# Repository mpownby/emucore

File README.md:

emucore
=======

Permissive high-quality emulation-related code

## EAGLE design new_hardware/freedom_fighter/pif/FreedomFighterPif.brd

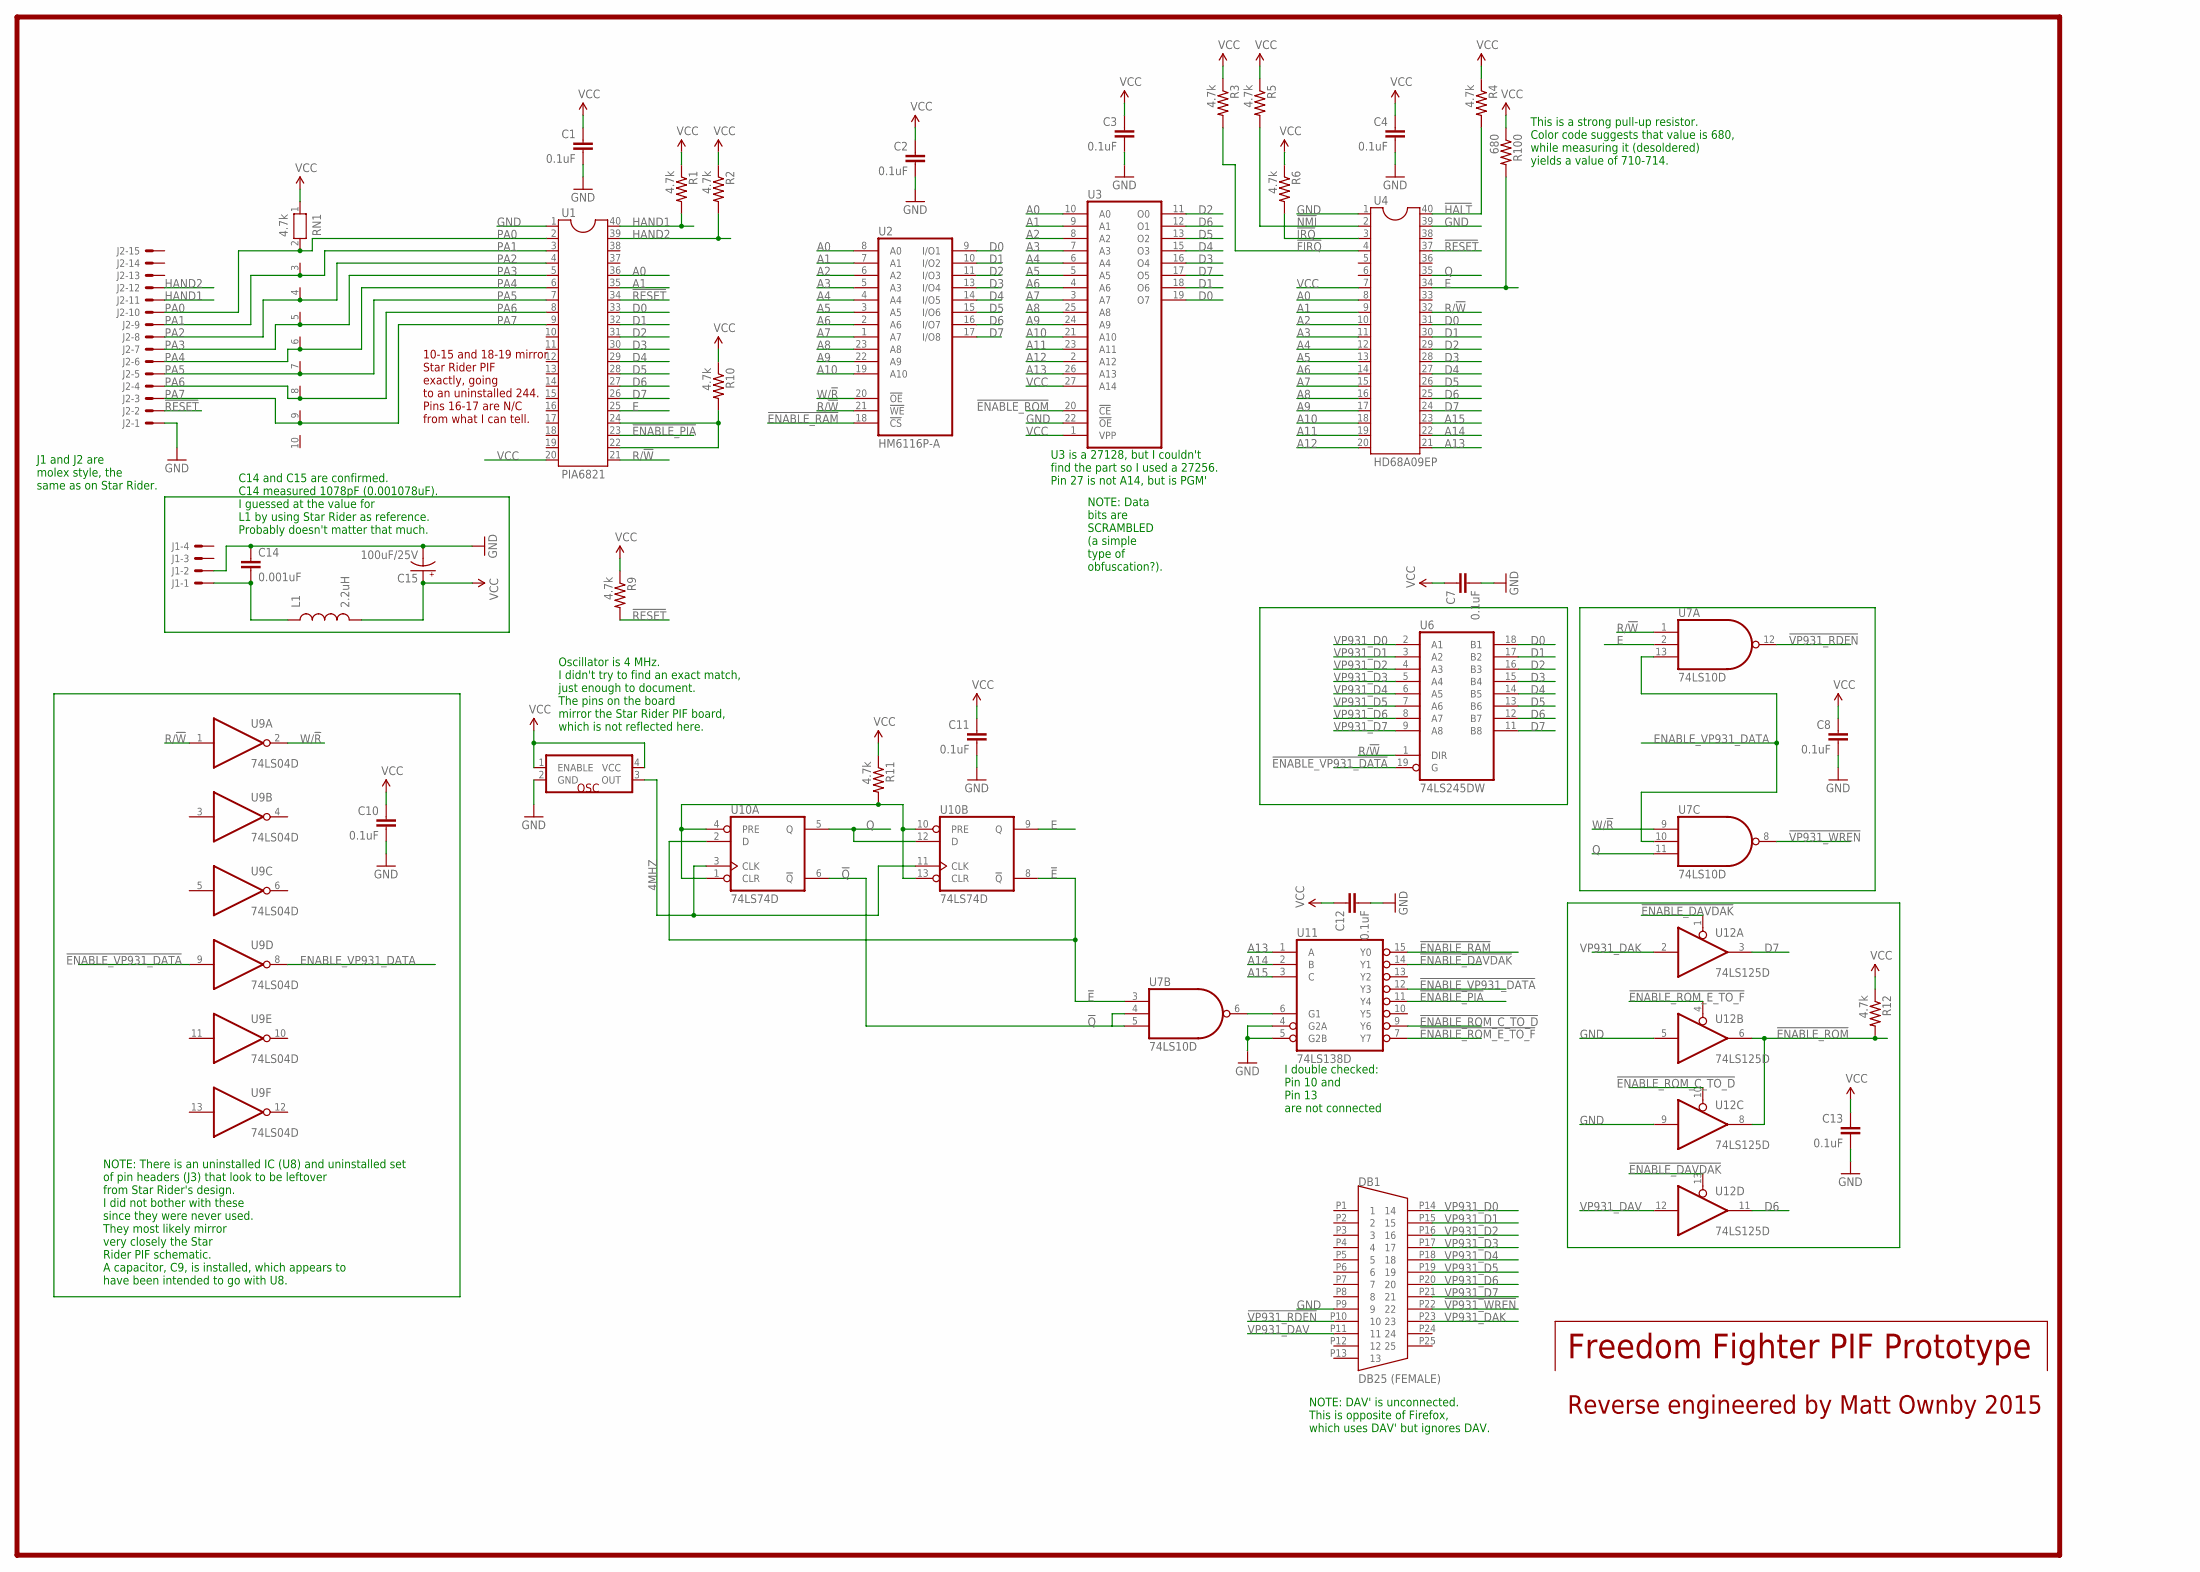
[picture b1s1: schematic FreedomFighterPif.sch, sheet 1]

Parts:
C1, C2, C3, C4, C7, C8, C10, C11, C12, C13: 0.1uF; 1206
C14: 0.001uF; 1206
C15: 100uF/25V; CPOL-RADIAL-10UF-25V
DB1: DB25 (FEMALE); A32077-ND
J1: KK-156-4
J2: KK-156-15
L1: 2.2uH; INDUCTOR-1206
R1, R2, R3, R4, R5, R6, R9, R10, R11, R12: 4.7k; 1206
R100: 680; 1206
RN1: 4.7k; RN-10
U1: PIA6821; DIL40
U2: HM6116P-A; SO24-2
U3: 27256; DIL28
U4: HD68A09EP; DIL40
U6: 74LS245DW; SO20W
U7: 74LS10D; SO14
U9: 74LS04D; SO14
U10: 74LS74D; SO14
U11: 74LS138D; SO16
U12: 74LS125D; SO14
U$1: OSCILLATOR-SMT4; SMT4-7MMX5MM

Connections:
4MHZ: U10.3 (CLK), U10.11 (CLK), U$1.3 (OUT)
!E: U7.3 (I0), U10.2 (D), U10.8 (!Q)
!ENABLE_DAVDAK: U11.14 (Y1), U12.1 (OE), U12.13 (OE); also elsewhere on the board
!ENABLE_PIA: U1.23, U11.11 (Y4); also elsewhere on the board
!ENABLE_RAM: U2.18 (!CS), U11.15 (Y0); also elsewhere on the board
!ENABLE_ROM: R12.2, U3.20 (!CE), U12.6 (O), U12.8 (O)
!ENABLE_ROM_C_TO_D: U11.9 (Y6), U12.10 (OE); also elsewhere on the board
!ENABLE_ROM_E_TO_F: U11.7 (Y7), U12.4 (OE); also elsewhere on the board
!ENABLE_VP931_DATA: U6.19 (G), U9.9 (I), U11.12 (Y3); also elsewhere on the board
!FIRQ: R3.2, U4.4; also elsewhere on the board
!HALT: R4.2, U4.40; also elsewhere on the board
!IRQ: R6.2, U4.3; also elsewhere on the board
!NMI: R5.2, U4.2; also elsewhere on the board
!Q: U7.4 (I1), U7.5 (I2), U10.6 (!Q)
!RESET: J2.2, R9.2, U1.34, U4.37; also elsewhere on the board
!VP931_RDEN: DB1.P10 (10), U7.12 (O)
!VP931_WREN: DB1.P22 (22), U7.8 (O)
A0: U1.36, U2.8 (A0), U3.10 (A0), U4.8; also elsewhere on the board
A1: U1.35, U2.7 (A1), U3.9 (A1), U4.9; also elsewhere on the board
A2: U2.6 (A2), U3.8 (A2), U4.10; also elsewhere on the board
A3: U2.5 (A3), U3.7 (A3), U4.11; also elsewhere on the board
A4: U2.4 (A4), U3.6 (A4), U4.12; also elsewhere on the board
A5: U2.3 (A5), U3.5 (A5), U4.13; also elsewhere on the board
A6: U2.2 (A6), U3.4 (A6), U4.14; also elsewhere on the board
A7: U2.1 (A7), U3.3 (A7), U4.15; also elsewhere on the board
A8: U2.23 (A8), U3.25 (A8), U4.16; also elsewhere on the board
A9: U2.22 (A9), U3.24 (A9), U4.17; also elsewhere on the board
A10: U2.19 (A10), U3.21 (A10), U4.18; also elsewhere on the board
A11: U3.23 (A11), U4.19; also elsewhere on the board
A12: U3.2 (A12), U4.20; also elsewhere on the board
A13: U3.26 (A13), U4.21, U11.1 (A); also elsewhere on the board
A14: U4.22, U11.2 (B); also elsewhere on the board
A15: U4.23, U11.3 (C); also elsewhere on the board
CS0/CS1: R10.2, U1.22, U1.24
D0: U1.33, U2.9 (I/O1), U3.19 (O7), U4.31, U6.18 (B1); also elsewhere on the board
D1: U1.32, U2.10 (I/O2), U3.18 (O6), U4.30, U6.17 (B2); also elsewhere on the board
D2: U1.31, U2.11 (I/O3), U3.11 (O0), U4.29, U6.16 (B3); also elsewhere on the board
D3: U1.30, U2.13 (I/O4), U3.16 (O4), U4.28, U6.15 (B4); also elsewhere on the board
D4: U1.29, U2.14 (I/O5), U3.15 (O3), U4.27, U6.14 (B5); also elsewhere on the board
D5: U1.28, U2.15 (I/O6), U3.13 (O2), U4.26, U6.13 (B6); also elsewhere on the board
D6: U1.27, U2.16 (I/O7), U3.12 (O1), U4.25, U6.12 (B7), U12.11 (O); also elsewhere on the board
D7: U1.26, U2.17 (I/O8), U3.17 (O5), U4.24, U6.11 (B8), U12.3 (O); also elsewhere on the board
E: R100.2, U1.25, U4.34, U7.2 (I1), U10.9 (Q); also elsewhere on the board
ENABLE_VP931_DATA: U7.10 (I1), U7.13 (I2), U9.8 (O); also elsewhere on the board
GND: C1.2, C2.2, C3.2, C4.2, C7.2, C8.2, C10.2, C11.2, C12.2, C13.2, C14.1, C15.2 (-), DB1.P9 (9), J1.2, J2.1, U1.1, U2.12 (GND), U3.14 (GND), U3.22 (!OE), U4.1, U4.39, U6.10 (GND), U7.7 (GND), U9.7 (GND), U10.7 (GND), U11.4 (G2A), U11.5 (G2B), U11.8 (GND), U12.5 (I), U12.7 (GND), U12.9 (I), U$1.2 (GND); also elsewhere on the board
HAND1: J2.11, R1.2, U1.40; also elsewhere on the board
HAND2: J2.12, R2.2, U1.39; also elsewhere on the board
unnamed: U7.6 (O), U11.6 (G1)
unnamed: R11.2, U10.1 (CLR), U10.4 (PRE), U10.10 (PRE), U10.13 (CLR)
unnamed: C14.2, J1.1, L1.P$1 (1)
PA0: J2.10, RN1.2, U1.2; also elsewhere on the board
PA1: J2.9, RN1.3, U1.3; also elsewhere on the board
PA2: J2.8, RN1.4, U1.4; also elsewhere on the board
PA3: J2.7, RN1.5, U1.5; also elsewhere on the board
PA4: J2.6, RN1.6, U1.6; also elsewhere on the board
PA5: J2.5, RN1.7, U1.7; also elsewhere on the board
PA6: J2.4, RN1.8, U1.8; also elsewhere on the board
PA7: J2.3, RN1.9, U1.9; also elsewhere on the board
Q: U4.35, U7.11 (I2), U10.5 (Q), U10.12 (D); also elsewhere on the board
R/!W: U1.21, U2.21 (!WE), U4.32, U6.1 (DIR), U7.1 (I0), U9.1 (I); also elsewhere on the board
VCC: C1.1, C2.1, C3.1, C4.1, C7.1, C8.1, C10.1, C11.1, C12.1, C13.1, C15.1 (+), L1.P$2 (2), R1.1, R2.1, R3.1, R4.1, R5.1, R6.1, R9.1, R10.1, R11.1, R12.1, R100.1, RN1.1, U1.20, U2.24 (VCC), U3.1 (VPP), U3.27 (A14), U3.28 (VCC), U4.7, U6.20 (VCC), U7.14 (VCC), U9.14 (VCC), U10.14 (VCC), U11.16 (VCC), U12.14 (VCC), U$1.1 (ENABLE), U$1.4 (VCC); also elsewhere on the board
VP931_D0: DB1.P14 (14), U6.2 (A1)
VP931_D1: DB1.P15 (15), U6.3 (A2)
VP931_D2: DB1.P16 (16), U6.4 (A3)
VP931_D3: DB1.P17 (17), U6.5 (A4)
VP931_D4: DB1.P18 (18), U6.6 (A5)
VP931_D5: DB1.P19 (19), U6.7 (A6)
VP931_D6: DB1.P20 (20), U6.8 (A7)
VP931_D7: DB1.P21 (21), U6.9 (A8)
VP931_DAK: DB1.P23 (23), U12.2 (I)
VP931_DAV: DB1.P11 (11), U12.12 (I)
W/!R: U2.20 (!OE), U7.9 (I0), U9.2 (O); also elsewhere on the board

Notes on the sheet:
U3 is a 27128, but I couldn't find the part so I used a 27256. Pin 27 is not A14, but is PGM'
NOTE: Data bits are SCRAMBLED (a simple type of obfuscation?).
I double checked: Pin 10 and Pin 13 are not connected
NOTE: There is an uninstalled IC (U8) and uninstalled set of pin headers (J3) that look to be leftover from Star Rider's design. I did not bother with these since they were never used. They most likely mirror very closely the Star Rider PIF schematic. A capacitor, C9, is installed, which appears to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
NOTE: DAV' is unconnected. This is opposite of Firefox, which uses DAV' but ignores DAV.
Oscillator is 4 MHz. I didn't try to find an exact match, just enough to document. The pins on the board mirror the Star Rider PIF board, which is not reflected here.
C14 and C15 are confirmed. C14 measured 1078pF (0.001078uF). I guessed at the value for L1 by using Star Rider as reference. Probably doesn't matter that much.
Freedom Fighter PIF Prototype
Reverse engineered by Matt Ownby 2015
10-15 and 18-19 mirror Star Rider PIF exactly, going to an uninstalled 244. Pins 16-17 are N/C from what I can tell.
This is a strong pull-up resistor. Color code suggests that value is 680, while measuring it (desoldered) yields a value of 710-714.
J1 and J2 are molex style, the same as on Star Rider.

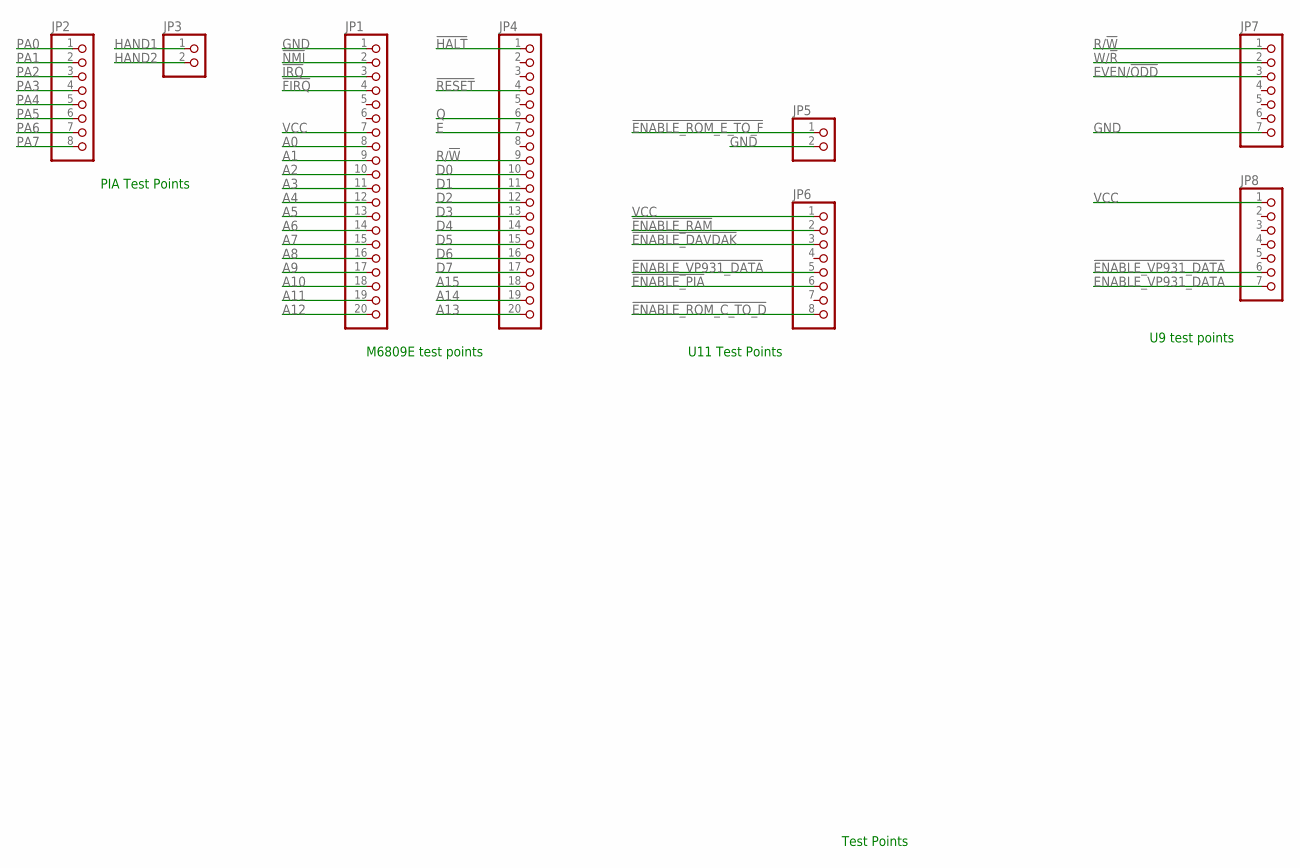
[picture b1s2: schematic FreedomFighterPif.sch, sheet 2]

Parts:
JP1, JP4: PINHD-1X20; 1X20
JP2, JP6: PINHD-1X8; 1X08
JP3, JP5: PINHD-1X2; 1X02
JP7, JP8: PINHD-1X7; 1X07

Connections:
!ENABLE_DAVDAK: JP6.3; also elsewhere on the board
!ENABLE_PIA: JP6.6; also elsewhere on the board
!ENABLE_RAM: JP6.2; also elsewhere on the board
!ENABLE_ROM_C_TO_D: JP6.8; also elsewhere on the board
!ENABLE_ROM_E_TO_F: JP5.1; also elsewhere on the board
!ENABLE_VP931_DATA: JP6.5, JP8.6; also elsewhere on the board
!FIRQ: JP1.4; also elsewhere on the board
!HALT: JP4.1; also elsewhere on the board
!IRQ: JP1.3; also elsewhere on the board
!NMI: JP1.2; also elsewhere on the board
!RESET: JP4.4; also elsewhere on the board
A0: JP1.8; also elsewhere on the board
A1: JP1.9; also elsewhere on the board
A2: JP1.10; also elsewhere on the board
A3: JP1.11; also elsewhere on the board
A4: JP1.12; also elsewhere on the board
A5: JP1.13; also elsewhere on the board
A6: JP1.14; also elsewhere on the board
A7: JP1.15; also elsewhere on the board
A8: JP1.16; also elsewhere on the board
A9: JP1.17; also elsewhere on the board
A10: JP1.18; also elsewhere on the board
A11: JP1.19; also elsewhere on the board
A12: JP1.20; also elsewhere on the board
A13: JP4.20; also elsewhere on the board
A14: JP4.19; also elsewhere on the board
A15: JP4.18; also elsewhere on the board
D0: JP4.10; also elsewhere on the board
D1: JP4.11; also elsewhere on the board
D2: JP4.12; also elsewhere on the board
D3: JP4.13; also elsewhere on the board
D4: JP4.14; also elsewhere on the board
D5: JP4.15; also elsewhere on the board
D6: JP4.16; also elsewhere on the board
D7: JP4.17; also elsewhere on the board
E: JP4.7; also elsewhere on the board
ENABLE_VP931_DATA: JP8.7; also elsewhere on the board
EVEN/!ODD: JP7.3
GND: JP1.1, JP5.2, JP7.7; also elsewhere on the board
HAND1: JP3.1; also elsewhere on the board
HAND2: JP3.2; also elsewhere on the board
PA0: JP2.1; also elsewhere on the board
PA1: JP2.2; also elsewhere on the board
PA2: JP2.3; also elsewhere on the board
PA3: JP2.4; also elsewhere on the board
PA4: JP2.5; also elsewhere on the board
PA5: JP2.6; also elsewhere on the board
PA6: JP2.7; also elsewhere on the board
PA7: JP2.8; also elsewhere on the board
Q: JP4.6; also elsewhere on the board
R/!W: JP4.9, JP7.1; also elsewhere on the board
VCC: JP1.7, JP6.1, JP8.1; also elsewhere on the board
W/!R: JP7.2; also elsewhere on the board

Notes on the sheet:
PIA Test Points
M6809E test points
U11 Test Points
U9 test points
Test Points

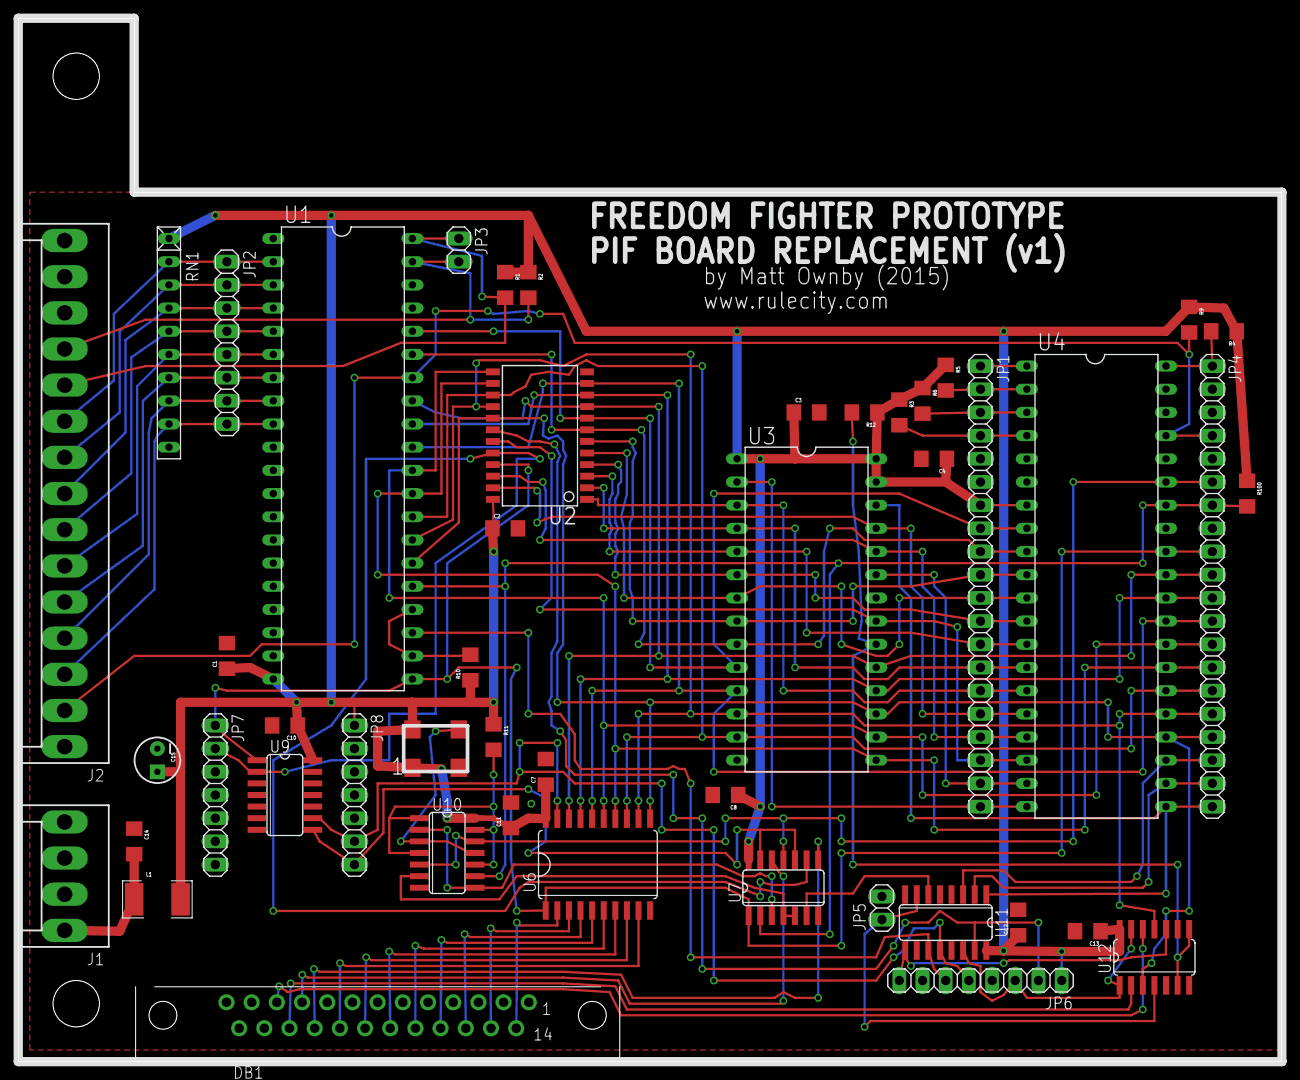
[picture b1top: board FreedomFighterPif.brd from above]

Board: 2 copper layers, 138.4 x 114.3 mm, 47 parts (0 on the bottom side), 72 nets.

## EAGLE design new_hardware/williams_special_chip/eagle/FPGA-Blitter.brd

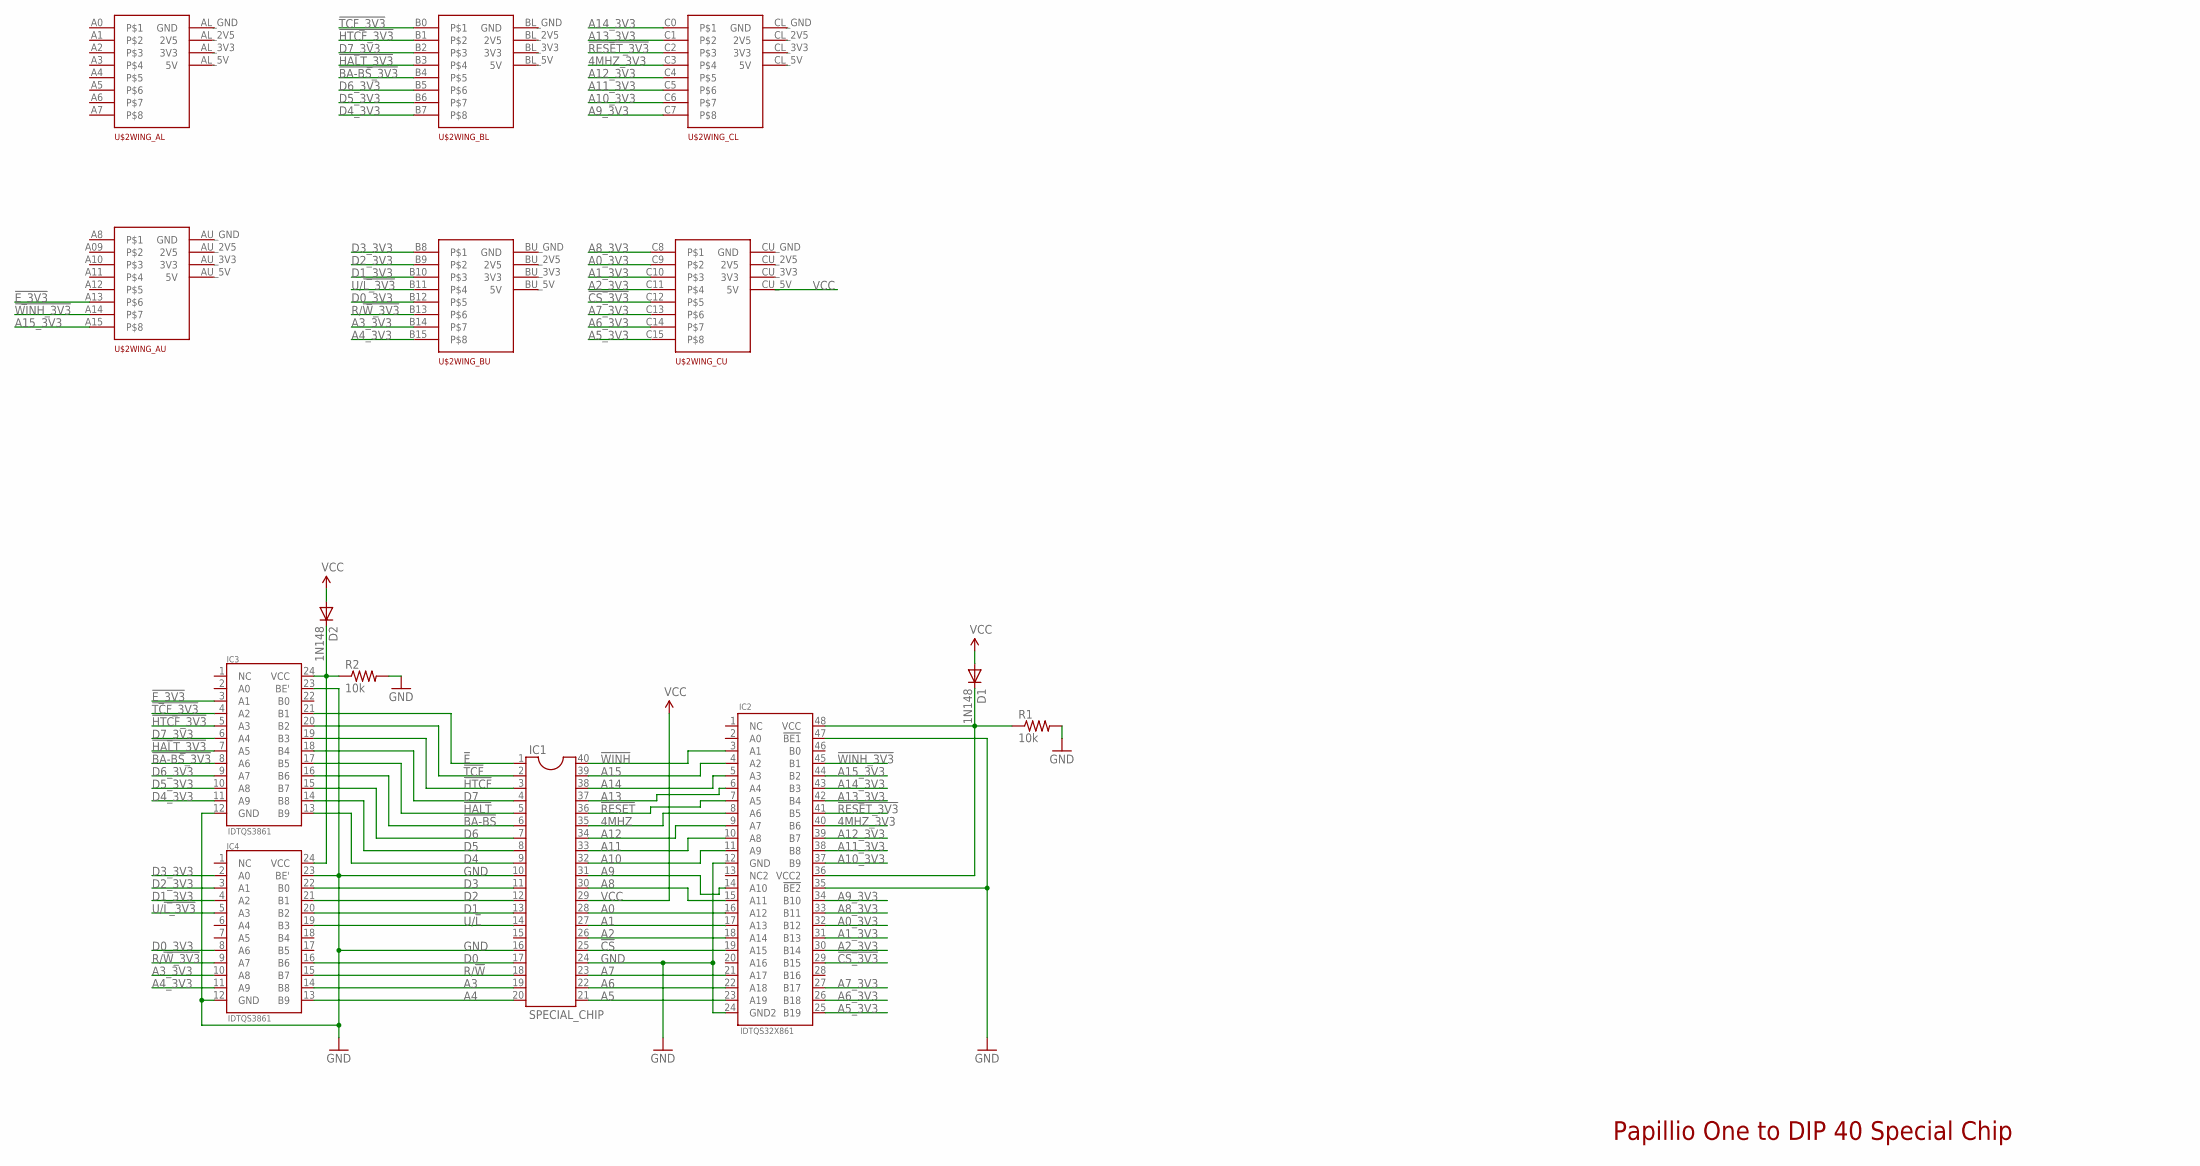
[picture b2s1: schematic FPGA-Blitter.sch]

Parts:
D1, D2: 1N148; DIODE-1N4148
IC1: SPECIAL_CHIP; DIL40
IC2: IDTQS32X861; QVSOP-DJG48-IDT
IC3, IC4: IDTQS3861; TSSOP24
R1, R2: 10k; 1206
U$2: PAPILIO48

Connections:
4MHZ: IC1.35, IC2.8 (A6)
4MHZ_3V3: IC2.40 (B6), U$2.C3
!BA-BS: IC1.6, IC3.16 (B6)
!BA-BS_3V3: IC3.8 (A6), U$2.B4
!CS: IC1.25, IC2.19 (A15)
!CS_3V3: IC2.29 (B15), U$2.C12
!E: IC1.1, IC3.21 (B1)
!E_3V3: IC3.3 (A1), U$2.A13
!HALT: IC1.5, IC3.17 (B5)
!HALT_3V3: IC3.7 (A5), U$2.B3
!HTCF: IC1.3, IC3.19 (B3)
!HTCF_3V3: IC3.5 (A3), U$2.B1
!RESET: IC1.36, IC2.7 (A5)
!RESET_3V3: IC2.41 (B5), U$2.C2
!TCF: IC1.2, IC3.20 (B2)
!TCF_3V3: IC3.4 (A2), U$2.B0
!WINH: IC1.40, IC2.3 (A1)
!WINH_3V3: IC2.45 (B1), U$2.A14
A0: IC1.28, IC2.16 (A12)
A0_3V3: IC2.32 (B12), U$2.C9
A1: IC1.27, IC2.17 (A13)
A1_3V3: IC2.31 (B13), U$2.C10
A2: IC1.26, IC2.18 (A14)
A2_3V3: IC2.30 (B14), U$2.C11
A3: IC1.19, IC4.14 (B8)
A3_3V3: IC4.10 (A8), U$2.B14
A4: IC1.20, IC4.13 (B9)
A4_3V3: IC4.11 (A9), U$2.B15
A5: IC1.21, IC2.23 (A19)
A5_3V3: IC2.25 (B19), U$2.C15
A6: IC1.22, IC2.22 (A18)
A6_3V3: IC2.26 (B18), U$2.C14
A7: IC1.23, IC2.21 (A17)
A7_3V3: IC2.27 (B17), U$2.C13
A8: IC1.30, IC2.15 (A11)
A8_3V3: IC2.33 (B11), U$2.C8
A9: IC1.31, IC2.14 (A10)
A9_3V3: IC2.34 (B10), U$2.C7
A10: IC1.32, IC2.11 (A9)
A10_3V3: IC2.37 (B9), U$2.C6
A11: IC1.33, IC2.10 (A8)
A11_3V3: IC2.38 (B8), U$2.C5
A12: IC1.34, IC2.9 (A7)
A12_3V3: IC2.39 (B7), U$2.C4
A13: IC1.37, IC2.6 (A4)
A13_3V3: IC2.42 (B4), U$2.C1
A14: IC1.38, IC2.5 (A3)
A14_3V3: IC2.43 (B3), U$2.C0
A15: IC1.39, IC2.4 (A2)
A15_3V3: IC2.44 (B2), U$2.A15
D0: IC1.17, IC4.16 (B6)
D0_3V3: IC4.8 (A6), U$2.B12
D1: IC1.13, IC4.20 (B2)
D1_3V3: IC4.4 (A2), U$2.B10
D2: IC1.12, IC4.21 (B1)
D2_3V3: IC4.3 (A1), U$2.B9
D3: IC1.11, IC4.22 (B0)
D3_3V3: IC4.2 (A0), U$2.B8
D4: IC1.9, IC3.13 (B9)
D4_3V3: IC3.11 (A9), U$2.B7
D5: IC1.8, IC3.14 (B8)
D5_3V3: IC3.10 (A8), U$2.B6
D6: IC1.7, IC3.15 (B7)
D6_3V3: IC3.9 (A7), U$2.B5
D7: IC1.4, IC3.18 (B4)
D7_3V3: IC3.6 (A4), U$2.B2
GND: IC1.10, IC1.16, IC1.24, IC2.12 (GND), IC2.24 (GND2), IC2.35 (!BE2), IC2.47 (!BE1), IC3.12 (GND), IC3.23 (BE'), IC4.12 (GND), IC4.23 (BE'), R1.2, R2.2
unnamed: D2.C, IC3.24 (VCC), IC4.24 (VCC), R2.1
unnamed: D1.C, IC2.36 (VCC2), IC2.48 (VCC), R1.1
R/!W: IC1.18, IC4.15 (B7)
R/!W_3V3: IC4.9 (A7), U$2.B13
U/!L: IC1.14, IC4.19 (B3)
U/!L_3V3: IC4.5 (A3), U$2.B11
VCC: D1.A, D2.A, IC1.29, U$2.CU_5V (5V)

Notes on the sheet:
Papillio One to DIP 40 Special Chip

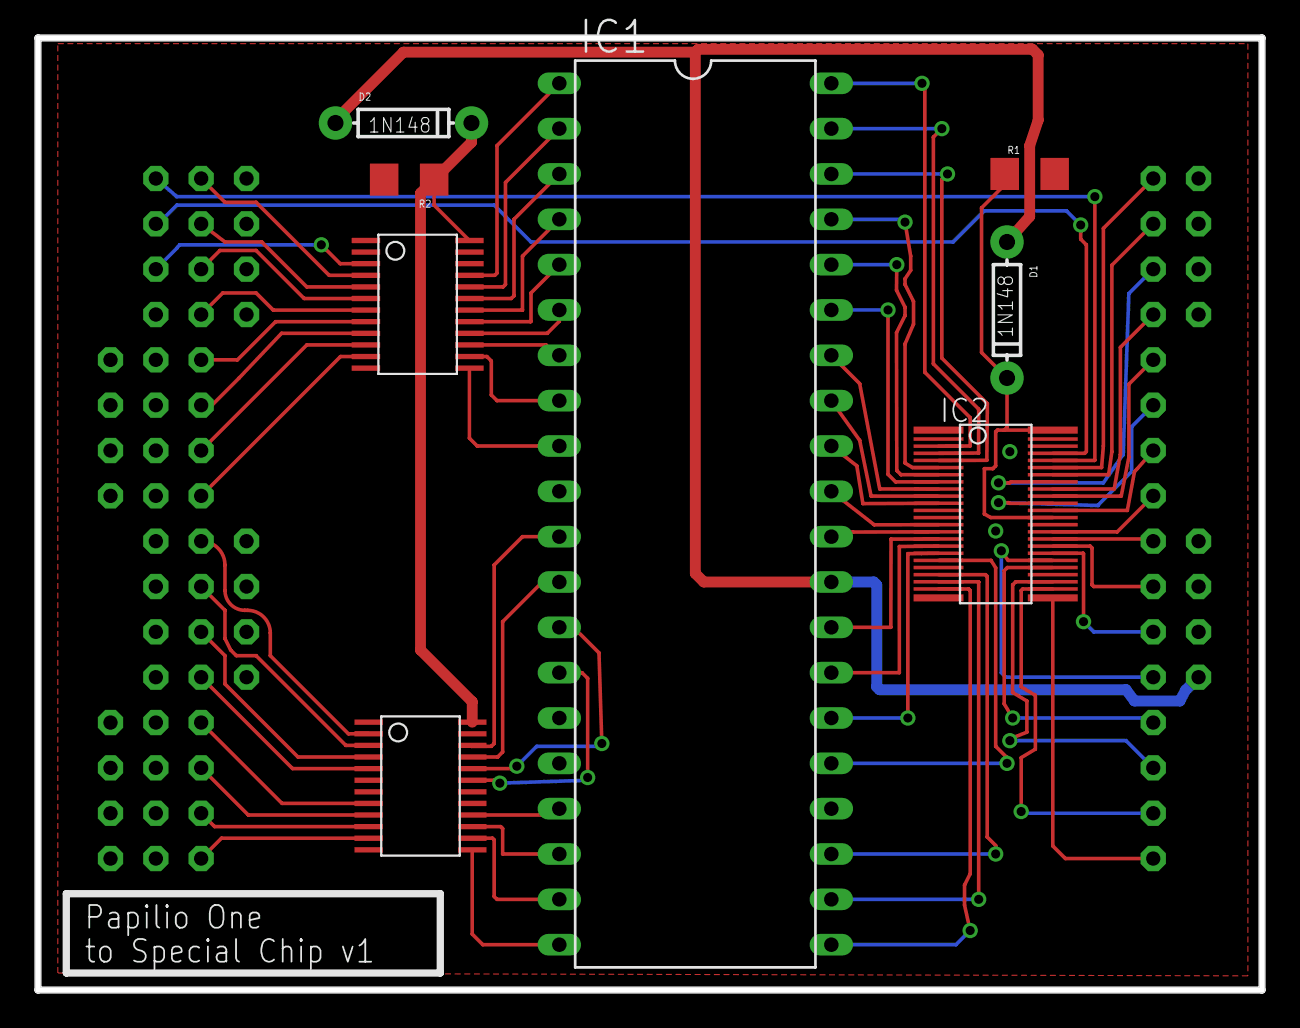
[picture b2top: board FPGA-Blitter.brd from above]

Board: 2 copper layers, 68.6 x 53.3 mm, 9 parts (1 on the bottom side), 74 nets.

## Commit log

2014-01-29 added IDA v3.85b ".idb" files of partial disassemblies that I've done over the years
2014-01-29 added proper segments for space ace .IDB file, added disassembly text file
2014-01-29 added star rider main cpu disassembly
2014-01-31 added a bunch of segments
2014-01-31 more disassembly
2014-01-31 added other ROMs successfully
2014-01-31 added disassembly for page 4 of the main cpu
2014-01-31 more progress, may have found PIF hello stuff
2014-02-02 added star rider schematics with comments
2014-02-02 made more progress on memory map
2014-02-03 added more VGG schematics
2014-02-05 more notes added to schematics, more disassembly done
2014-02-12 added ROM schematic, updated other schematics and disassembly
2014-02-18 more disassembly update, schematic updates
2014-02-19 added VGG5/5 schematic, updated disassembly
2014-02-22 added expander schematic, more disassembly of main cpu
2014-02-22 updated disassembly
2014-02-26 more disassembly...
2014-03-01 more progress on disassembly
2014-03-02 disassembly 1 March
2014-03-04 disassembly 3 mar 2014
2014-05-07 syncing up, don't remember what changes I made
2014-08-05 added eagle files for preliminary FPGA Blitter
2014-08-05 added datasheets for IDT quickswitch
2014-08-05 added 20 I/O line quickswitch part. about to try auto-router
2014-08-05 got one half finished
2014-08-06 gotta just verify pins chosen and this is ready for production
2014-08-06 added note about current
2014-08-06 added preliminary
2014-08-06 fixed initial check-in files
2014-08-06 updated to match Blitter PCB design
2014-08-06 tweaks
2014-08-06 a few touch-ups to board layout
2014-08-10 added intro process (to load registers)
2014-08-11 - moved CLK_4MHZ and E_N to global clock pins on the FPGA - added another process to help detect CS authentically
2014-08-14 added galaxy ranger
2014-09-01 added AVR and java projects for Williams IC Tester
2014-09-01 added post-build event so that .bin file is always created on building
2014-09-02 started working on special chip tester
2014-10-15 added dragon's lair and time traveler disassembly/game/lair/dl_f2.idb Some more work on williams IC tester
2015-03-02 added new disassembly of firefox, updated disassembly of dragon's lair and added a note on star rider schematic
2015-03-12 - updated firefox disassembly (vp-931 I/O stuff) - update dragon's lair disassembly (cleared up how pr-7820 stuff works) - fixed star rider schematic error (modified schematic to reflect PCB modifica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
2015-03-18 added firefox schematic of part of ntsc demod board
2015-03-20 renamed
2015-03-20 added freedom fighter pif board schematics, board layout, and photograph
2015-03-20 did more reverse engineering of freedom fighter pif board
2015-03-20 more reverse engineering
2015-03-21 added FFR PIF disassembly and updated PIF schematics
2015-03-23 almost done with schematic, did some more disassembling
2015-03-23 Essentially finished schematic, started laying out PCB
2015-03-24 Schematic is "final", but I will be removing stuff from it to make the board so I am saving it
2015-03-24 added PIF schematic
2015-03-24 completed about half of the routing. I'd say the hard part is done.
2015-03-25 3/4 of the way finished, about to add ground plane
2015-03-25 about to submit v1
2015-03-25 submitted!
2015-03-26 updated schematic with notes from measurements
2015-05-27 new disassembly for thayer's quest, firefox, freedom fighter, and dragon's lair
2015-10-30 a bit more work on dragon's lair and thayer's quest disassemblies. Got rid of IntelliJ-specific stuff for the WilliamsIcTester in favor of Maven (future change).
2015-10-30 added star rider PIF disassembly
2015-11-17 (updated IDA version to v6.8) A lot more disassembly added, specifically, the portions responsible for sending commands to the PIF board and checking to see whether a seek was successful.
2015-11-19 decoded FIRQ section among other things
2016-02-25 updated star rider, time traveler disassembly and star rider schematic
2016-02-25 started adding proper segments
2016-02-25 making progress on segmenting timetrav
2016-02-26 found the still step fwd command
2016-03-04 more work on TT disasssembly
2016-03-10 updated star rider disassembly
2016-03-11 added an ltspice simulation for the star rider main cpu watchdog circuit
2016-04-26 updated time traveler disassembly, star rider watch dog simulation. updated freedom fighter pif disassembly to latest ida but didn't actually make any changes.
2016-06-08 made a lot of progress on the firefox disassembly (converted to ida v6.9)
2016-10-10 added a cliff hanger zpu1/2 and gsi schematics
2016-10-10 added schematic for zpu 2/2, updated schematic for zpu 1/2
2016-10-11 updated cliffy disassembly, added junctions to zpu schematic using PCB as reference
2016-10-11 compressed GIMP files, updated zpu 1/2 schematic
2016-10-27 updated DL f2 disassembly, updated cliff hanger GSI schematic
2016-10-27 - updated cliffy ZPU 1/2 with some notes on RAM. - updated star rider VGG 1/5 with some notes on the RGB circuit.
2016-11-30 added a second version of the same page :)
2017-01-30 added scan of top and bottom of cliffy UIB PCB
2017-02-23 updated disassembly for star rider and time traveler
2017-07-13 updated diassembly for esh and star rider
2017-07-20 did more work on esh disassembly
2017-07-29 added esh picture
2018-01-02 - updated star rider VGG 5/5 with info about the biphase decoding - updated disassembly of esh, thayer's quest, star rider main cpu
2018-01-03 clarified a few things on vgg 5/5
2020-03-09 updated DL F2 and star rider disassemblies
2021-02-02 added updates to DL and Esh disassemblies. Added disassembly of dragon's lair Rev A 68705 microcontroller program.
2021-11-06 added new DL disassembly. Added warning message to FFR PIF board.
2022-03-28 - added preliminary disassembly for cobra command and dragon's lair 2 - added schematic scans from bega's battle
2023-03-16 added a bunch of new star rider schematics
2023-03-16 added rest of star rider schematics
2026-05-09 decoded laserdics commands in halcyon ROM
2026-05-29 made progress on halcyon disassembly, relating to speech recognition path

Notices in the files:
parts and their libraries:
SparkFun: Licensing: CC v3.0 Share-Alike You are welcome to use this library for commercial purposes.
